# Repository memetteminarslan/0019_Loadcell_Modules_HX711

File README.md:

# 0019_Loadcell_Modules_HX711
You are seeing a large number of widely used load cell modules in electronic development kits. More information coming soon...

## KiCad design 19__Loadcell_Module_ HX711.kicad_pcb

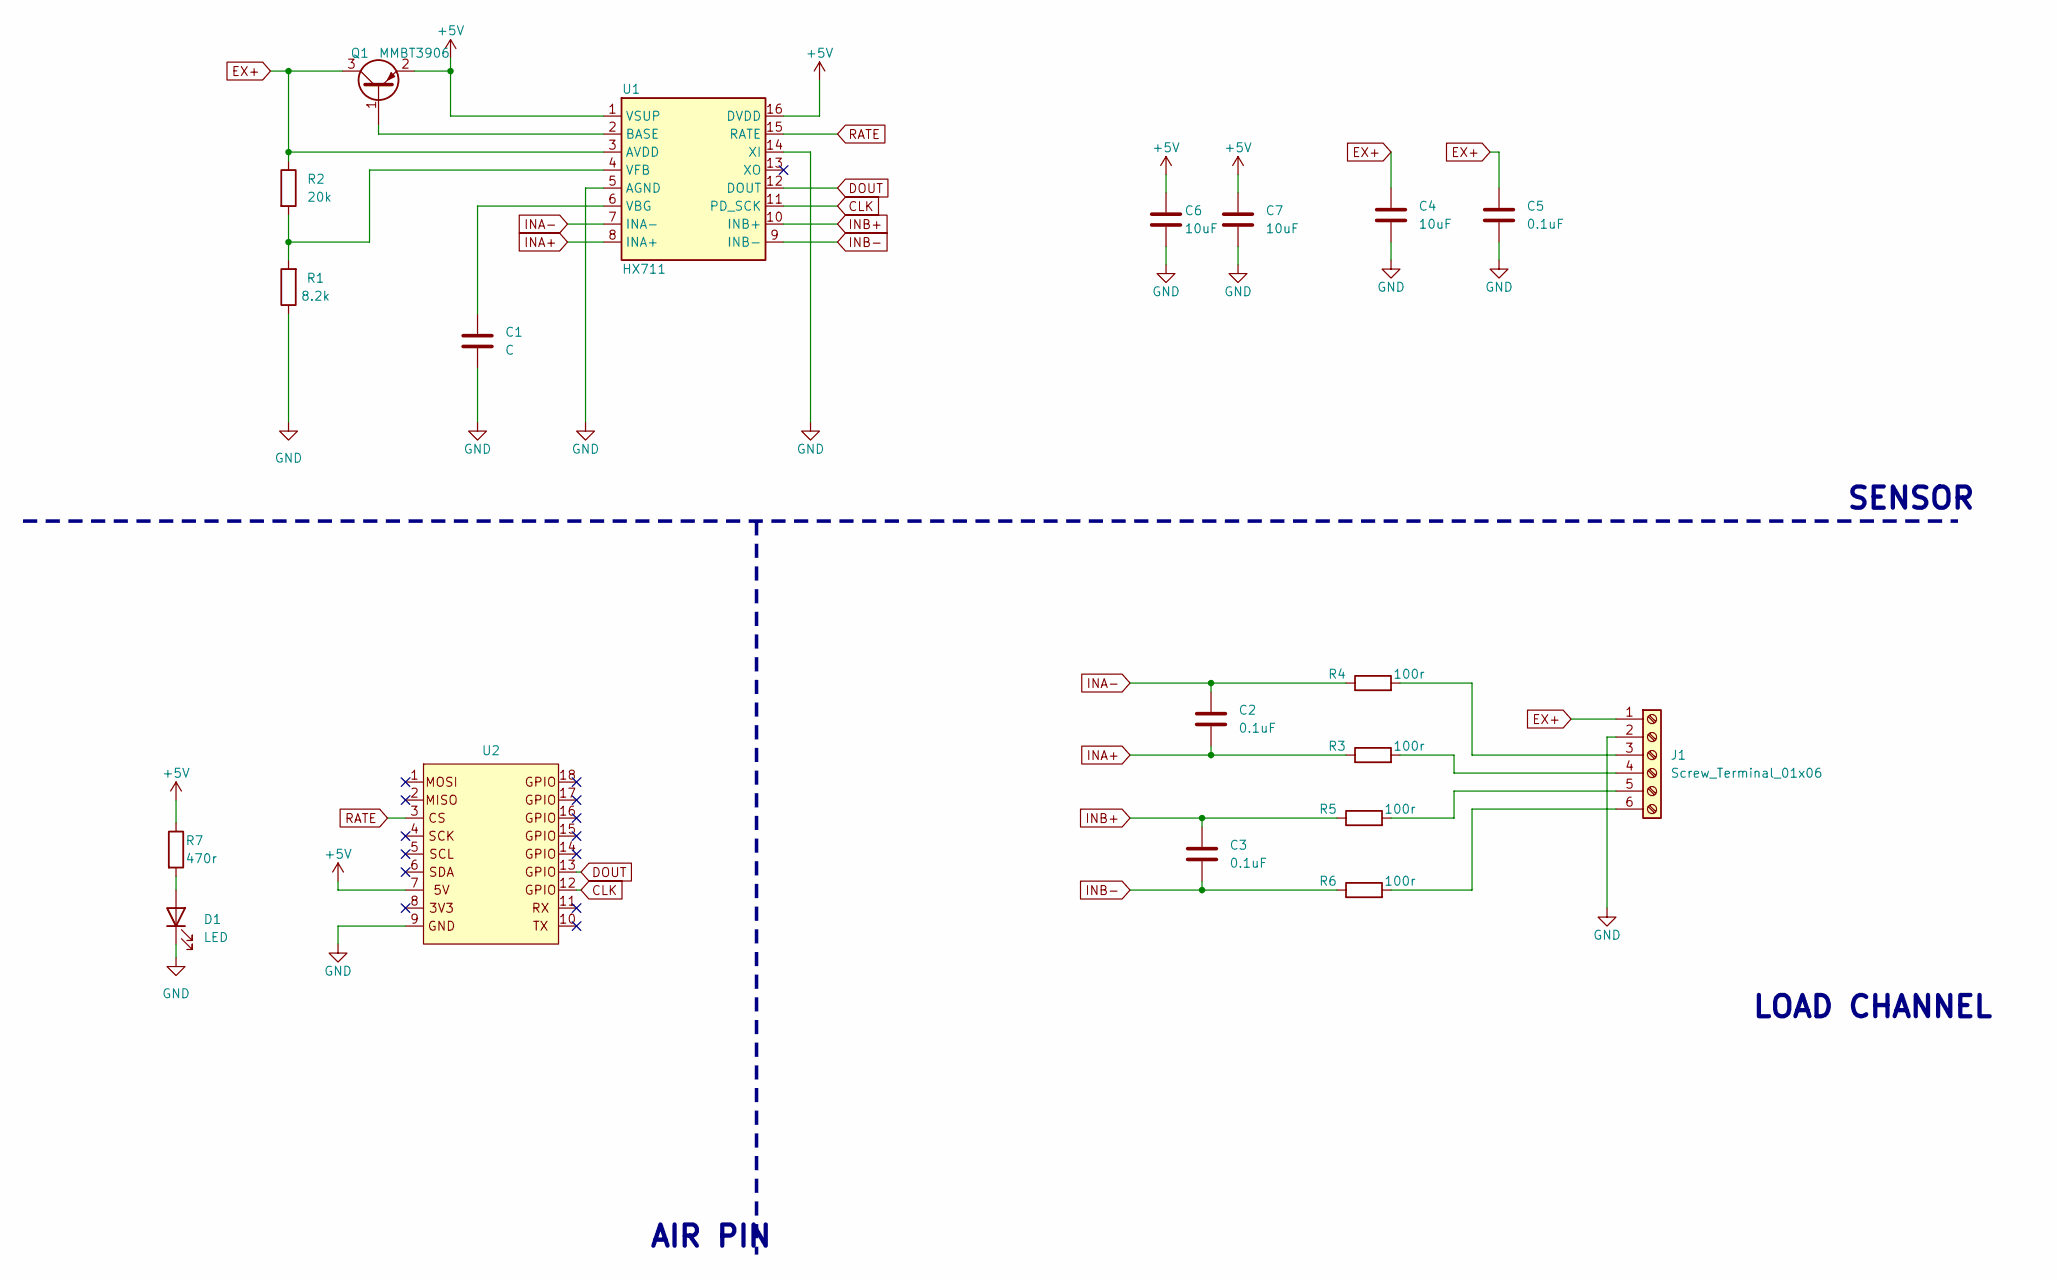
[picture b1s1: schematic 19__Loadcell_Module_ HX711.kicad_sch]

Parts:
C1: C; C_0805_2012Metric
C2, C3, C5: 0.1uF; C_0805_2012Metric
C4, C6, C7: 10uF; C_0805_2012Metric
D1: LED; LED_0805_2012Metric
J1: Screw_Terminal_01x06; TerminalBlock_Phoenix_PT-1,5-6-3.5-H_1x06_P3.50mm_Horizontal
Q1: MMBT3906; SOT-23
R1: 8.2k; R_0805_2012Metric
R2: 20k; R_0805_2012Metric
R3, R4, R5, R6: 100r; R_0805_2012Metric
R7: 470r; R_0805_2012Metric
U1: HX711; SOP-16_3.9x9.9mm_P1.27mm
U2: pin_header

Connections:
+5V: C6.1, C7.1, Q1.2 (E), R7.1, U2.7; also elsewhere on the board
CLK: U1.11 (PD_SCK), U2.12; also elsewhere on the board
DOUT: U1.12 (DOUT), U2.13; also elsewhere on the board
EX+: C4.1, C5.1, J1.1, Q1.3 (C), R2.1, U1.3 (AVDD); also elsewhere on the board
GND: C1.2, C4.2, C5.2, C6.2, C7.2, D1.1 (K), J1.2, R1.1, U1.5 (AGND), U1.14 (XI), U2.9; also elsewhere on the board
INA+: C2.2, R3.1, U1.8 (INA+); also elsewhere on the board
INA-: C2.1, R4.1, U1.7 (INA-); also elsewhere on the board
INB+: C3.1, R5.1, U1.10 (INB+); also elsewhere on the board
INB-: C3.2, R6.1, U1.9 (INB-); also elsewhere on the board
unnamed: D1.2 (A), R7.2
unnamed: J1.3, R4.2
unnamed: J1.4, R3.2
unnamed: J1.5, R5.2
unnamed: J1.6, R6.2
unnamed 14: Q1.1 (B), U1.2 (BASE); also elsewhere on the board
unnamed 15: C1.1, U1.6 (VBG); also elsewhere on the board
unnamed 16: R1.2, R2.2, U1.4 (VFB); also elsewhere on the board
RATE: U1.15 (RATE), U2.3; also elsewhere on the board

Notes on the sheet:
AIR PIN
LOAD CHANNEL
SENSOR

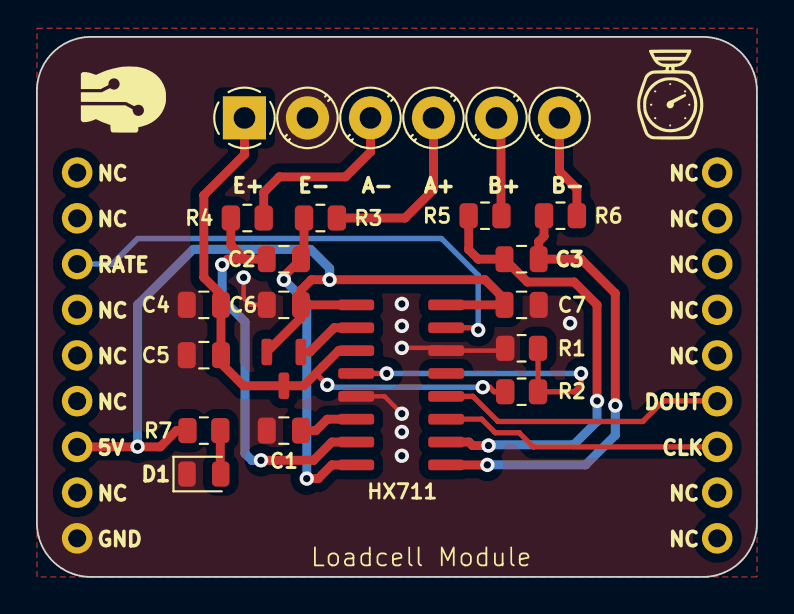
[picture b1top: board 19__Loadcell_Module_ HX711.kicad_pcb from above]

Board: 2 copper layers, 40.0 x 30.0 mm, 19 parts (0 on the bottom side), 18 nets.

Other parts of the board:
HX711: HX711; SOP-16_3.9x9.9mm_P1.27mm

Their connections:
+5V: HX711.1 (VSUP), HX711.16 (DVDD); also elsewhere on the board
CLK: HX711.11 (PD_SCK); also elsewhere on the board
DOUT: HX711.12 (DOUT); also elsewhere on the board
EX+: HX711.3 (AVDD); also elsewhere on the board
GND: HX711.5 (AGND), HX711.14 (XI); also elsewhere on the board
INA+: HX711.8 (INA+); also elsewhere on the board
INA-: HX711.7 (INA-); also elsewhere on the board
INB+: HX711.10 (INB+); also elsewhere on the board
INB-: HX711.9 (INB-); also elsewhere on the board
unnamed 14: HX711.2 (BASE); also elsewhere on the board
unnamed 15: HX711.6 (VBG); also elsewhere on the board
unnamed 16: HX711.4 (VFB); also elsewhere on the board
RATE: HX711.15 (RATE); also elsewhere on the board
